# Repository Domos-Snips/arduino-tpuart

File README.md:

Arduino EIB/KNX Interface via TP-UART
=====================================

This is a very first version of an interface between Arduino and EIB/KNX using the TP-UART interface and Arduino library.

Last modified: 12.08.2017

Reason: Added link to library

Hardware
--------

We leverage Siemens BCU 5WG1 117-2AB12 - for about ~30€

-> Please note: When using an additional power supply galvanic separation between ARDUINO and BCU is necessary.

We leverage ARDUINO MEGA (SERIAL PORT 1)

-> No restrictions on the programming

We leverage ARDUINO UNO (SERIAL PORT)

-> During programming, the BCU may have no connection to the ARDUINO UNO.

-> After programming for communication with the BCU. Connect the jumpers ICSP1 PIN 5 and ICSP1 PIN 6 together, tested only with ARDUINO UNO revision 3.

-> For programming the jumper ICSP1 PIN 5 and ICSP1 PIN 6 must be not connected together and the voltage must be taken away for a short time. Then, you can transfer the new "sketch". 

Software (library was tested with IDE 1.0.5-R2 , IDE 1.6.9  and IDE 1.8.1 by arduino.cc)
---------------------------------------------------------------------------

The Arduino library is found in the directory `KnxTpUart` and can be directly placed in Arduino's library folder. 

Issues, Comments and Suggestions
--------------------------------

If you have any, don't hesitate to contact me or use the issue tracker. You are also invited to improve the code and send me a pull request to reintegrate the changes here.

Supported commands / telegram types
-----------------------------------
All commando (write) to bus :
-----------------------------

Bool (DPT 1 - 0 or 1)

knx.groupWriteBool("1/2/3", bool);

4 Bit Int (DPT 3)

knx.groupWrite4BitInt("1/2/3", int);

4 Bit Dim (DPT 3)

knx.groupWrite4BitDim("1/2/3", direction, steps);

1 Byte Int (DPT 5 - 0...255)

knx.groupWrite1ByteInt("1/2/3", int);

2 Byte Int (DPT 7 - 0…65 535])

knx.groupWrite2ByteInt("1/2/3", int);

2 Byte Float (DPT 9 - -671 088,64 to 670 760,96 )

knx.groupWrite2ByteFloat("1/2/3", float);

3 Byte Time (DPT 10)

groupWrite3ByteTime("1/2/3", Weekday, Hour, Minute, Second);

3 Byte Date (DPT 11)

groupWrite3ByteDate("1/2/3", Day, Month, Year);

4 byte Float (DPT 14 - -2147483648 to 2147483647) 

knx.groupWrite4ByteFloat("1/2/3", float);

14 Byte Text (DPT 16)

knx.groupWrite14ByteText("1/2/3", String);

All commando (answer) to bus :
------------------------------

Bool (DPT 1 - 0 or 1)

knx.groupAnswerBool("1/2/3", bool);

4 Bit Int (DPT 3)

commented out -> knx.groupAnswer4BitInt("1/2/3", int);

4 Bit Int (DPT 3)

commented out -> knx.groupWrite4BitDim("1/2/3", bool, byte);

1 Byte Int (DPT 5 - 0...255)

knx.groupAnswer1ByteInt("1/2/3", int);

2 Byte Int (DPT 7 - 0…65 535])

knx.groupAnswer2ByteInt("1/2/3", int);

2 Byte Float (DPT 9 - -671 088,64 to 670 760,96 )

knx.groupAnswer2ByteFloat("1/2/3", float);

3 Byte Time (DPT 10)

knx.groupAnswer3ByteTime("1/2/3", int, int, int, int);

3 Byte Date (DPT 11)

knx.groupAnswer3ByteDate("1/2/3", int, int, int);

4 byte Float (DPT 14 - -2147483648 to 2147483647)

knx.groupAnswer4ByteFloat("1/2/3", float);

14 Byte Text (DPT 16)

knx.groupAnswer14ByteText("1/2/3", String);

Once for all DPT -> commando (read) to bus :
--------------------------------------------

knx.groupRead("1/2/3");

Evaluation telegrams from bus :
-------------------------------

Bool (DPT 1 - 0 or 1)

value = telegram->getBool();

4 Bit Int (DPT 3)

value = telegram->get4BitIntValue();

Bool (DPT 3)

value = telegram->get4BitDirectionValue();

1 byte (DPT 3)

value = telegram->get4BitStepsValue();

1 Byte Int (DPT 5 - 0...255)

value = telegram->get1ByteIntValue();

2 Byte Int (DPT 7 - 0…65 535])

value = telegram->get2ByteIntValue();

2 Byte Float (DPT 9 - -671 088,64 to 670 760,96 )

value = telegram->get2ByteFloatValue();

3 Byte Time (DPT 10)

value = telegram->get3ByteWeekdayValue();

3 Byte Time (DPT 10)

value = telegram->get3ByteHourValue();

3 Byte Time (DPT 10)

value = telegram->get3ByteMinuteValue();

3 Byte Time (DPT 10)

value = telegram->get3ByteSecondValue();

3 Byte Time (DPT 11)

value = telegram->get3ByteDayValue();

3 Byte Time (DPT 11)

value = telegram->get3ByteMonthValue();

3 Byte Time (DPT 11)

value = telegram->get3ByteYearValue();

4 byte Float (DPT 14 - -2147483648 to 2147483647)

value = telegram->get4ByteFloatValue();

14 Byte Text (DPT 16)

value = telegram->get14ByteValue();

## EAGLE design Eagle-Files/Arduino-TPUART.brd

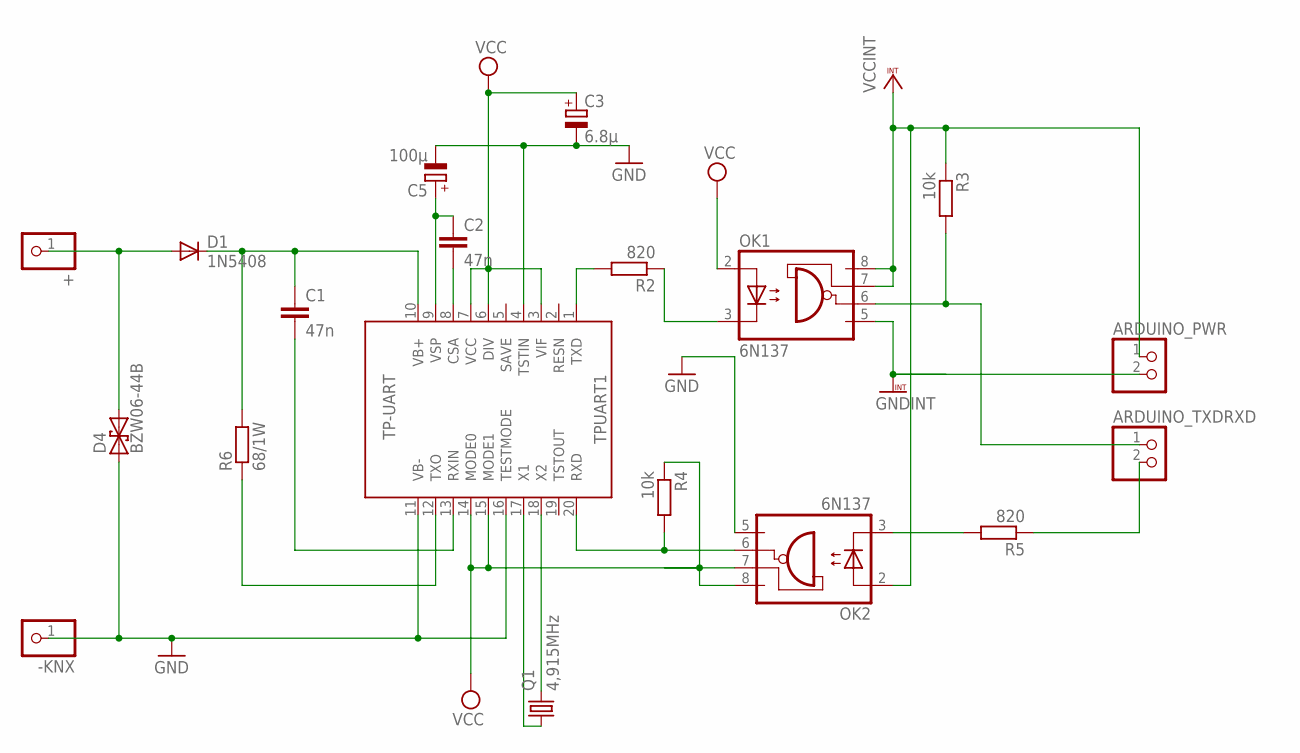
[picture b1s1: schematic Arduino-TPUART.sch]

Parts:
+: PINHD-1X1; 1X01
-KNX: PINHD-1X1; 1X01
ARDUINO_PWR: PINHD-1X2; 1X02
ARDUINO_TXDRXD: PINHD-1X2; 1X02
C1, C2: 47n; C025-025X050
C3: 6.8µ; E2-5
C5: 100µ; E2,5-5
D1: 1N5408; DO201-15
D4: BZW06-44B; F126Z12
OK1, OK2: 6N137; DIL08
Q1: 4,915MHz; HC18U-V
R2, R5: 820; 0411/12
R3, R4: 10k; 0411/12
R6: 68/1W; 0414/15
TPUART1: TP-UART; SOIC20

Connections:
ARDUINO_RXD: ARDUINO_TXDRXD.1, OK1.6 (VO), R3.2
ARDUINO_TXD: ARDUINO_TXDRXD.2, R5.1
GND: -KNX.1, C3.-, C5.-, D4.A (1), OK2.5 (GND), TPUART1.4 (TSTIN), TPUART1.11 (VB-), TPUART1.16 (TESTMODE)
GNDINT: ARDUINO_PWR.2, OK1.5 (GND)
KNX+: +.1, D1.A, D4.C (2)
unnamed: C1.1, D1.C, R6.2, TPUART1.10 (VB+)
unnamed: R6.1, TPUART1.12 (TXO)
unnamed: C1.2, TPUART1.13 (RXIN)
unnamed: C2.2, TPUART1.8 (CSA)
unnamed: C2.1, C5.+, TPUART1.9 (VSP)
unnamed: Q1.1, TPUART1.17 (X1)
unnamed: Q1.2, TPUART1.18 (X2)
unnamed: R2.2, TPUART1.1 (TXD)
unnamed: OK1.3 (C), R2.1
unnamed: OK2.6 (VO), R4.2, TPUART1.20 (RXD)
unnamed: OK2.3 (C), R5.2
VCC: C3.+, OK1.2 (A), OK2.7 (VE), OK2.8 (VCC), R4.1, TPUART1.3 (VIF), TPUART1.6 (DIV), TPUART1.7 (VCC), TPUART1.14 (MODE0), TPUART1.15 (MODE1)
VCCINT: ARDUINO_PWR.1, OK1.7 (VE), OK1.8 (VCC), OK2.2 (A), R3.1

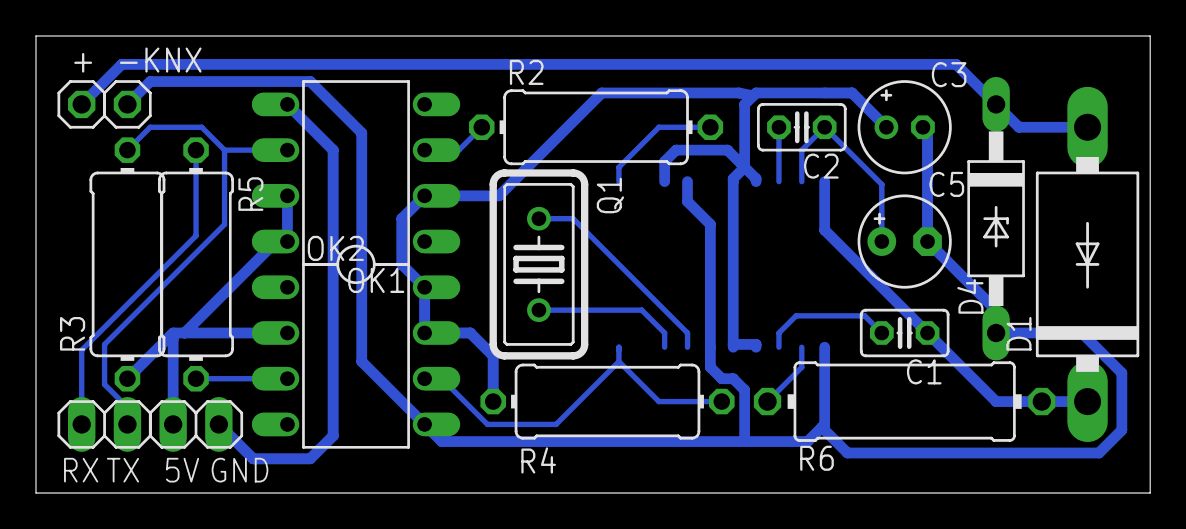
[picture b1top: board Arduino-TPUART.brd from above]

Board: 2 copper layers, 61.9 x 25.4 mm, 19 parts (1 on the bottom side), 18 nets.

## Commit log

2012-01-14 Initial checkin.
2012-01-14 Add first example.
2012-01-14 Add Eagle schematic.
2012-01-14 Add README.
2012-01-15 Add physical address as constructor argument. Fixes #2 Add more examples. Implement reply to read request.
2012-01-16 Update README with links.
2012-01-16 Update schematic with actually used parts and their correct packages.
2012-01-16 Fix typo.
2012-01-18 Add Eclipse project descriptors. Add first unit tests. See #3 Begin refactoring out the diagram parsing to the new class KnxTelegram.
2012-01-18 Refactor KNX command constants to their own enum.
2012-01-18 Add getters and setters for all message properties. Add appropriate unit tests. Configure build to use Arduino sources.
2012-01-18 Update examples and fix sending.
2012-01-19 See #4 Add methods to add listen group addresses. On incoming telegram verify it is relevant and send appropriate answer to TP-UART.
2012-01-19 Reply with correct event type depending on the relevance of the telegram. Such, clients can easily only use relevant telegrams. See #4
2012-01-20 Add a method to retrieve the total telegram length.
2012-01-20 Wait for confirmation and return true/false depending on the success of the transmission. Closes #4
2012-01-20 Support for writing and receiving 2-Byte-Floats (DPT 9.xxx, e.g. temperatures).
2012-01-20 Care for repetitions on sending telegram. Add example for creating a KNX temperature sensor using a Dallas One-Wire sensor.
2013-01-01 Add board layout for putting the KNX adapter on a breadboard.
2013-03-29 Add learning of individual address.
2013-03-29 Eclipse and Xcode metadata
2013-11-05 Make lib more universal to ease using on Due.
2014-01-25 README.md edited online with Bitbucket
2014-01-25 Arduino-TPUART.brd deleted online with Bitbucket
2014-01-25 Arduino-TPUART.sch deleted online with Bitbucket
2014-01-25 org.eclipse.cdt.codan.core.prefs deleted online with Bitbucket
2014-01-25 dka.mode1v3 deleted online with Bitbucket
2014-01-25 dka.pbxuser deleted online with Bitbucket
2014-01-25 project.pbxproj deleted online with Bitbucket
2014-01-25 contents.xcworkspacedata deleted online with Bitbucket
2014-01-25 WorkspaceSettings.xcsettings deleted online with Bitbucket
2014-01-25 Adapted for UNO and MEGA, groupWrite2ByteInt, 2ByteFloat, 4ByteFloat und 14ByteText
2014-01-25 changes groupWrite14Byte to groupWrite14ByteText
2014-01-25 Initial Update
2014-01-25 fixed groupAnswer2ByteInt
2014-01-25 Some Debug-events limited to DEBUG = true
2014-01-25 UCSR0A for UNO, UCSR1A for MEGA, USART1 for DUE
2014-01-26 Serial_ durch HardwareSerial ersetzt.
2014-01-26 Kommentar erg?nzt
2014-01-26 Typo corrected
2014-01-26 get14ByteValue returns "" - have to fix the return string
2014-01-26 Changed SerialUSB to Serial (for Debug-Port)
2014-01-26 Fehler in groupAnswer4ByteFloat beseitigt: Answer statt Write
2014-01-26 get14ByteText (=receive text telegramms) fixed.
2014-01-26 .project deleted online with Bitbucket
2014-01-30 KnxTelegram::getBool() hinzugef?gt (danke Michael W.)
2014-01-30 MAX_LISTEN_GROUP_ADDRESSES now set to 15
2014-01-31 1ByteInt hinzugef?gt
2014-01-31 get1ByteIntValue / set1ByteIntValue eingebaut
2014-01-31 get1ByteIntValue() / set1ByteIntValue() / getBool()
2014-01-31 HardwareSerial durch USARTClass getauscht
2014-03-21 Changed from HardwareSerial to parent class Stream, for seamless support of different boards
2014-04-02 Added an optional delay (SERIAL_WRITE_DELAY_MS) that can be defined in KnxTpUart.h. If set, a delay will be included after sending packets to the bus (50 might be a good value).
2014-04-02 Made the debug code parts excludeable by the pre-compiler which results in a binary which is about 3/2kB smaller.
2014-04-04 fixed an error in the getBool routine
2014-04-04 tried to fix an error in set2ByteFloatValue
2014-04-27 setKNXTime eingef?gt
2014-04-27 groupWriteTime eingef?gt
2014-04-27 Bug in Payload-Lengh behoben
2014-04-28 Switched to real adresses (phy 1.2.3 and KO 1/2/3)
2014-04-28 Switched to real adresses
2014-04-28 added implemented commands/telegram type
2014-04-28 Adapted to real Addresses
2014-04-28 ReceiveKNXTelegrams.ino edited online with Bitbucket
2014-04-28 GroupWrite.ino edited online with Bitbucket
2014-04-28 ReplyToKNXRead.ino edited online with Bitbucket
2014-04-28 TemperatureReadoutOneWire.ino edited online with Bitbucket
2014-04-28 UnitTests.ino edited online with Bitbucket
2014-05-09 KnxTpUart.h edited online with Bitbucket
2014-05-09 KnxTpUart.cpp edited online with Bitbucket
2014-05-09 .hgignore deleted online with Bitbucket
2014-05-09 .cproject deleted online with Bitbucket
2014-05-09 test.h created online with Bitbucket
2014-05-09 test.h deleted online with Bitbucket
2015-11-17 get/set 2byteIntValue
2015-11-17 set/get2ByteInt gefixt
2015-11-17 get/set2ByteIntValue gefixt
2015-11-19 Adapted example to new way to address
2015-11-19 Adapted to new structure. Added many examples to receive telegrams.
2015-11-19 Adapted to new structure
2015-11-21 groupReadBool aufgenommen
2015-11-21 Groupread.ino created online with Bitbucket
2015-11-21 Groupread.ino wurden online mit Bitbucket bearbeitet
2015-11-21 UserInterfaceState.xcuserstate deleted online with Bitbucket
2015-11-22 groupReadBool und groupRead umbenannt
2015-11-22 Type gefixt
2015-11-22 groupReadBool in groupRead umbenannt
2015-11-22 Example ausgearbeitet
2015-11-22 read-requests listed
2015-11-22 README.md wurden online mit Bitbucket bearbeitet
2015-12-27 knx.addListenGroupAddress hinzugef?gt
2015-12-30 error fixed: missing " added
2015-12-30 String get14ByteValue(); eingef?gt
2015-12-30 String KnxTelegram::get14ByteValue() - korrigiert
2015-12-30 Fixed several missing semicolon, added LED setup
2016-02-13 String get14ByteValue(); korrigiert
2016-02-14 Mag Gyver KnxTelegram.h edited online with Bitbucket
2016-02-21 KnxTpUart.h wurden online mit Bitbucket bearbeitet
2016-02-21 KnxTpUart.cpp wurden online mit Bitbucket bearbeitet
2016-02-21 KnxTelegram.h wurden online mit Bitbucket bearbeitet
2016-02-21 KnxTelegram.cpp wurden online mit Bitbucket bearbeitet
2016-02-21 ReplyToKNXRead.ino wurden online mit Bitbucket bearbeitet
2016-02-21 ReceiveKNXTelegrams.ino wurden online mit Bitbucket bearbeitet
2016-03-01 GroupWrite.ino wurden online mit Bitbucket bearbeitet
2016-03-01 LearnKNXAddress.ino wurden online mit Bitbucket bearbeitet
2016-03-01 TemperatureReadoutOneWire.ino wurden online mit Bitbucket bearbeitet
2016-03-01 UnitTests.ino wurden online mit Bitbucket bearbeitet
2017-02-24 KnxTelegram.cpp edited online with Bitbucket
    get2ByteFloatValue() fixed. Bit was read, but sign variable ignored, so method returned positive floats only.
2017-02-25 get2ByteFloatValue() checked for error
2017-03-02 Delay in ms between sending of packets to the bus -> set default to 100ms
2017-03-02 Increase readability
2017-03-02 Supplementary data types
2017-03-02 Supplementary data types (DPT)
2017-03-02 Revision
2017-03-02 Translation into English
2017-03-02 Supplements for ARDUINO <-> BCU
2017-04-16 modified
2017-04-16 Information supplement
2017-04-28 SERIAL_READ_TIMEOUT_MS switched to 10ms - to ensure received telegrams are read complete. Thanks to Udo Galle
2017-05-14 Added function "Wait"
2017-05-14 modfified
2017-05-14 Added function "Wait" and troubleshooting multiple telegrams
2017-05-14 Sorted and structured
2017-05-14 Minimum default values for reading and writing fixed
2017-05-14 Display Error fixed
2017-05-17 Range of values from 10 to 1000 for Serial_Read_Timeout_MS
2017-05-17 Range of values from 10 to 1000 for Read_Timeout_MS
2017-05-23 deleted
2017-05-23 return
2017-05-23 delete
2017-05-25 KnxTpUart.h
2017-05-25 KnxTpUart.cpp
2017-05-25 KnxTelegram.h
2017-05-25 KnxTelegram.cpp
2017-05-25 README.md
2017-06-11 note galvanic Separation added
2017-06-11 README.md modified
2017-08-03 Clarity
2017-08-15 Version 06.06.2017
2017-08-15 Close branch MagGyver/version-06062017-1502763376016
2020-04-13 UNKNOWN to UNKNOW_EVENT
    to solve IRremote integration
2020-04-13 UNKNOWN to UNKNOWN_EVENT
    to solve IRremote integration
